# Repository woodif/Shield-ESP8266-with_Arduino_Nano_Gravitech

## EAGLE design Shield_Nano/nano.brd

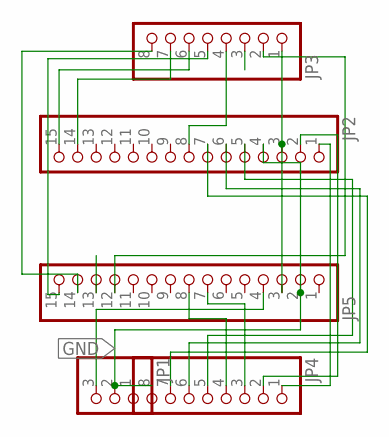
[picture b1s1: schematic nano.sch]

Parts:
JP1: PINHD-1X3CB; 1X03-CLEANBIG
JP2, JP5: PINHD-1X15; 1X15
JP3, JP4: PINHD-1X8CLEANBIG; 1X08-CLEANBIG

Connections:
GND: JP1.2, JP2.4, JP4.8, JP5.2
unnamed: JP1.3, JP5.4
unnamed: JP4.3, JP5.7
unnamed: JP4.4, JP5.8
unnamed: JP2.1, JP4.1
unnamed: JP2.2, JP4.2
unnamed: JP3.5, JP5.15
unnamed: JP2.15, JP3.6
unnamed: JP2.14, JP3.7
unnamed: JP2.5, JP4.5
unnamed: JP2.3, JP3.1, JP5.3
unnamed: JP3.2, JP5.12
unnamed: JP3.8, JP5.14
unnamed: JP2.6, JP4.6
unnamed: JP2.7, JP4.7
unnamed: JP2.8, JP3.4

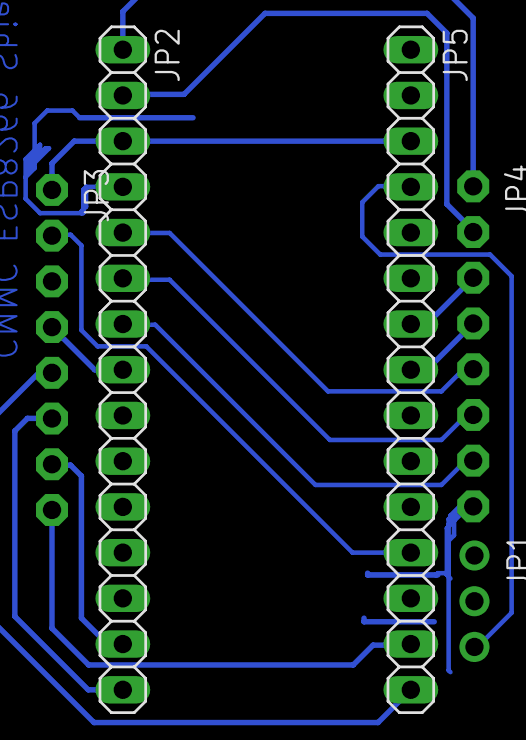
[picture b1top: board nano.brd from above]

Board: 2 copper layers, 5 parts (0 on the bottom side), 16 nets.

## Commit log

2015-06-24 Start
